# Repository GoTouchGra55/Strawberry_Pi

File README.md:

# 🍓 Strawberry Pi

A Raspberry Pi-4 form factor STM32 development board designed as a compact computing platform.

## Overview

Strawberry Pi is a custom 4-layer STM32-based development platform built around the **STM32H743** Cortex-M7 micro-controller.

The goal was to take the general concept of a small single-board computer and recreate it around a powerful micro-controller, integrating many useful interfaces and peripherals as possible into a compact Raspberry Pi 4 form factor.

The board is intended as a development and experimentation platform for hardware projects.

**SEE [SCHEMATICS](Strawberry_Pi-4.pdf)**

## Routing

## Features

### Core

- **STM32H743** Cortex-M7 MCU
- Up to **480 MHz** CPU clock
- MicroSD storage
- SWD debugging

### Connectivity

- **Ethernet**
- USB-C
- I2C
- SPI
- UART

### Multimedia

- Camera interface via **DCMI**
- Digital audio interface via **SAI**
- PCM1862 audio ADC
- 3.5 mm stereo audio input

### Power

The board provides dedicated:

- **5 V rail**
- **3.3 V rail**

## Rough BOM
| # | Item | Cost | Supplier |
|---|---|---:|---|
| 1 | PCB | $154.23 | JLCPCB |
| 2 | SMD Resistors | $8.35 | Daraz Nepal |
| 3 | SMD Capacitors | $7.98 | Daraz Nepal |
| | **Total** | **$170.56** | |

## Authors 👥

### Shaurya (Electronics)

Contact: [Email](shauryatamang.dev@gmail.com)

### Krish (CAD)

View: [Github](https://github.com/unknowngamer69/)

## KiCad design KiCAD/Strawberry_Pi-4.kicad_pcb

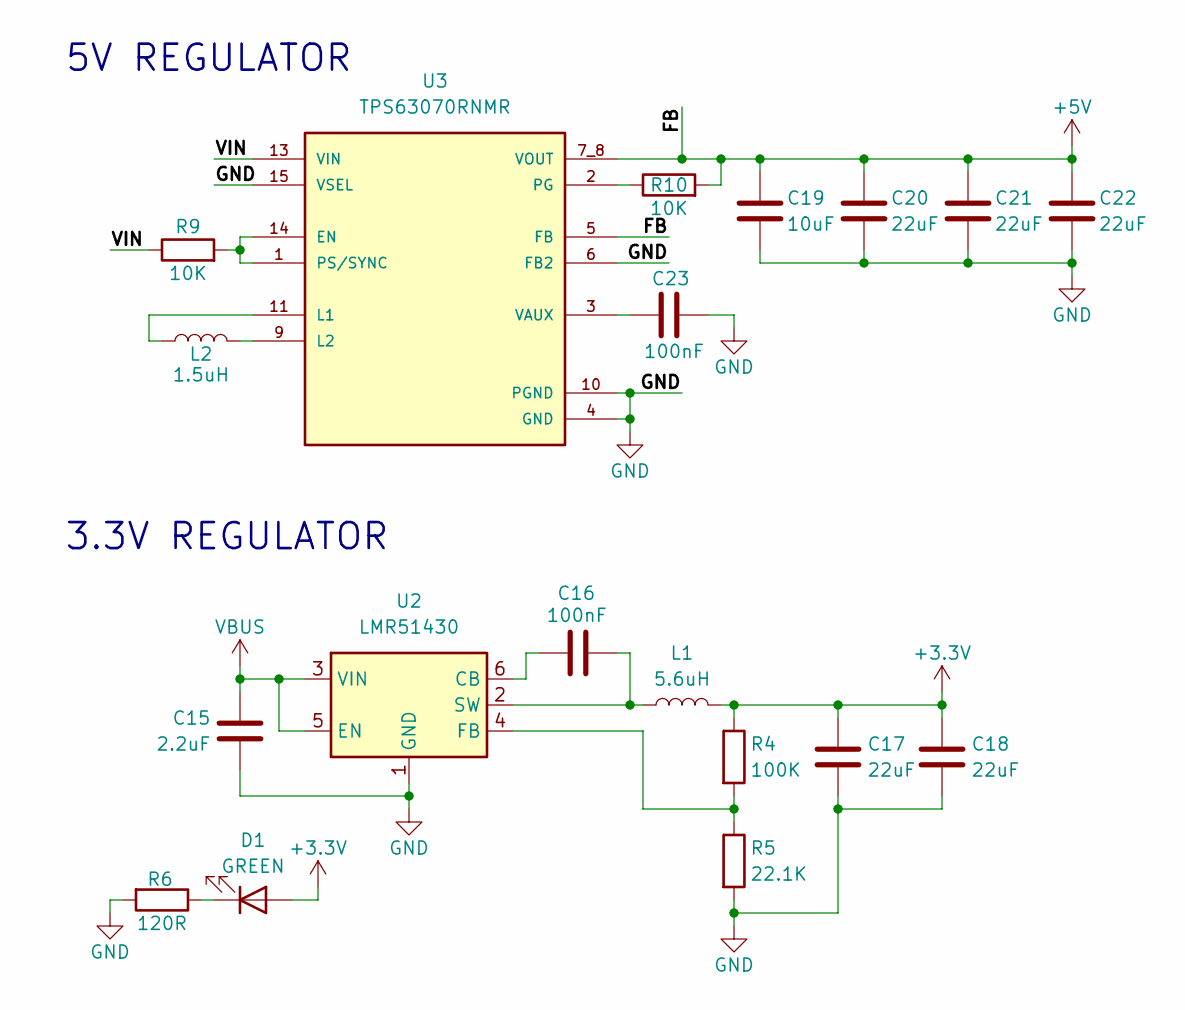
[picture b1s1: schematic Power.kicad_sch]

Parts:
C15: 2.2uF; C_0805_2012Metric
C16, C23: 100nF; C_0402_1005Metric
C17, C18, C20, C21, C22: 22uF; C_1210_3225Metric
C19: 10uF; C_0805_2012Metric
D1: GREEN; LED_0603_1608Metric
L1: 5.6uH; L_Wurth_WE-LQSH-2512
L2: 1.5uH; L_Wurth_WE-LQSH-4020
R4: 100K; R_0805_2012Metric
R5: 22.1K; R_0805_2012Metric
R6: 120R; R_0603_1608Metric
R9, R10: 10K; R_0603_1608Metric
U2: LMR51430; SOT-23-6
U3: TPS63070RNMR; VREG_TPS63070RNMR; PARTREV B

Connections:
+3.3V: C17.1, C18.1, D1.2 (A), L1.2, R4.1; also elsewhere on the board
+5V: C19.1, C20.1, C21.1, C22.1, R10.2, U3.5 (FB), U3.7_8 (VOUT); also elsewhere on the board
/Power/VIN: R9.1, U3.13 (VIN)
GND: C15.2, C17.2, C18.2, C19.2, C20.2, C21.2, C22.2, C23.2, R5.2, R6.2, U2.1 (GND), U3.4 (GND), U3.6 (FB2), U3.10 (PGND), U3.15 (VSEL); also elsewhere on the board
unnamed: D1.1 (K), R6.1
unnamed: C16.2, U2.6 (CB)
unnamed: R4.2, R5.1, U2.4 (FB)
unnamed: C16.1, L1.1, U2.2 (SW)
unnamed: R9.2, U3.1 (PS/SYNC), U3.14 (EN)
unnamed: L2.1, U3.11 (L1)
unnamed: L2.2, U3.9 (L2)
unnamed: R10.1, U3.2 (PG)
unnamed: C23.1, U3.3 (VAUX)
VBUS: C15.1, U2.3 (VIN), U2.5 (EN); also elsewhere on the board

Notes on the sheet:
5V REGULATOR
3.3V REGULATOR

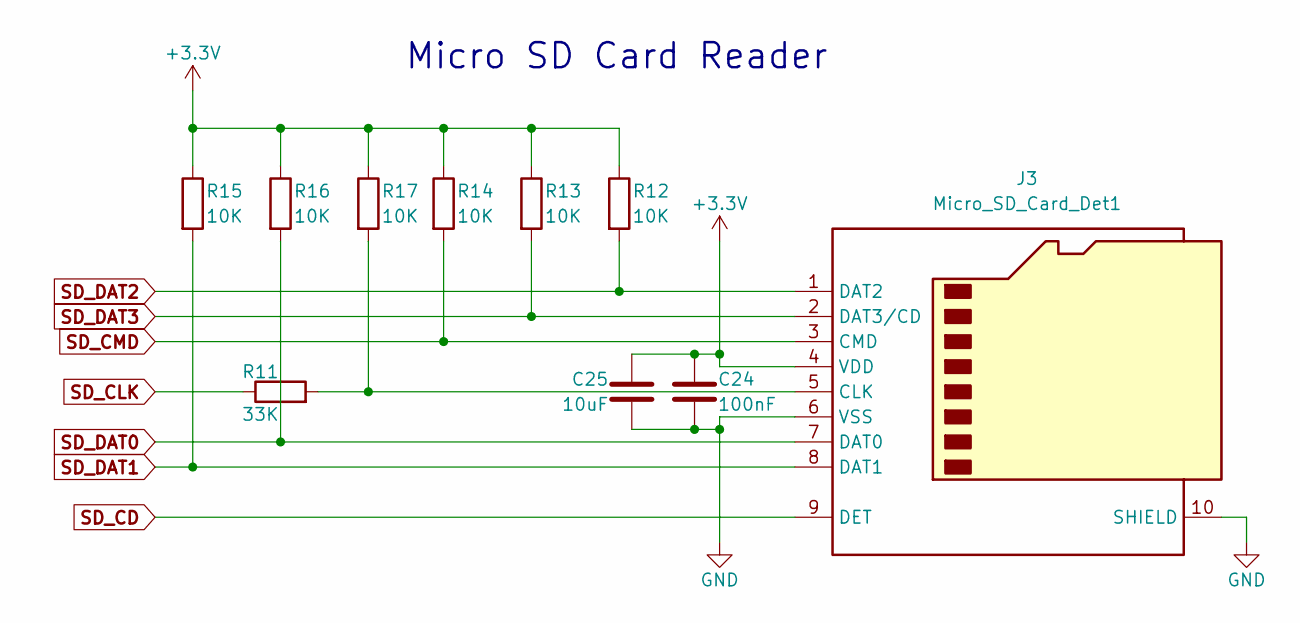
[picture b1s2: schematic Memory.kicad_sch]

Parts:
C24: 100nF; C_0402_1005Metric
C25: 10uF; C_0805_2012Metric
J3: Micro_SD_Card_Det1; microSD_HC_Wuerth
R11: 33K; R_0603_1608Metric
R12, R13, R14, R15, R16, R17: 10K; R_0603_1608Metric

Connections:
+3.3V: C24.1, C25.1, J3.4 (VDD), R12.1, R13.1, R14.1, R15.1, R16.1, R17.1; also elsewhere on the board
GND: C24.2, C25.2, J3.6 (VSS), J3.10 (SHIELD); also elsewhere on the board
unnamed: J3.5 (CLK), R11.2, R17.2
SD_CD: J3.9 (DET); also elsewhere on the board
SD_CLK: R11.1; also elsewhere on the board
SD_CMD: J3.3 (CMD), R14.2; also elsewhere on the board
SD_DAT0: J3.7 (DAT0), R16.2; also elsewhere on the board
SD_DAT1: J3.8 (DAT1), R15.2; also elsewhere on the board
SD_DAT2: J3.1 (DAT2), R12.2; also elsewhere on the board
SD_DAT3: J3.2 (DAT3/CD), R13.2; also elsewhere on the board

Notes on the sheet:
Micro SD Card Reader

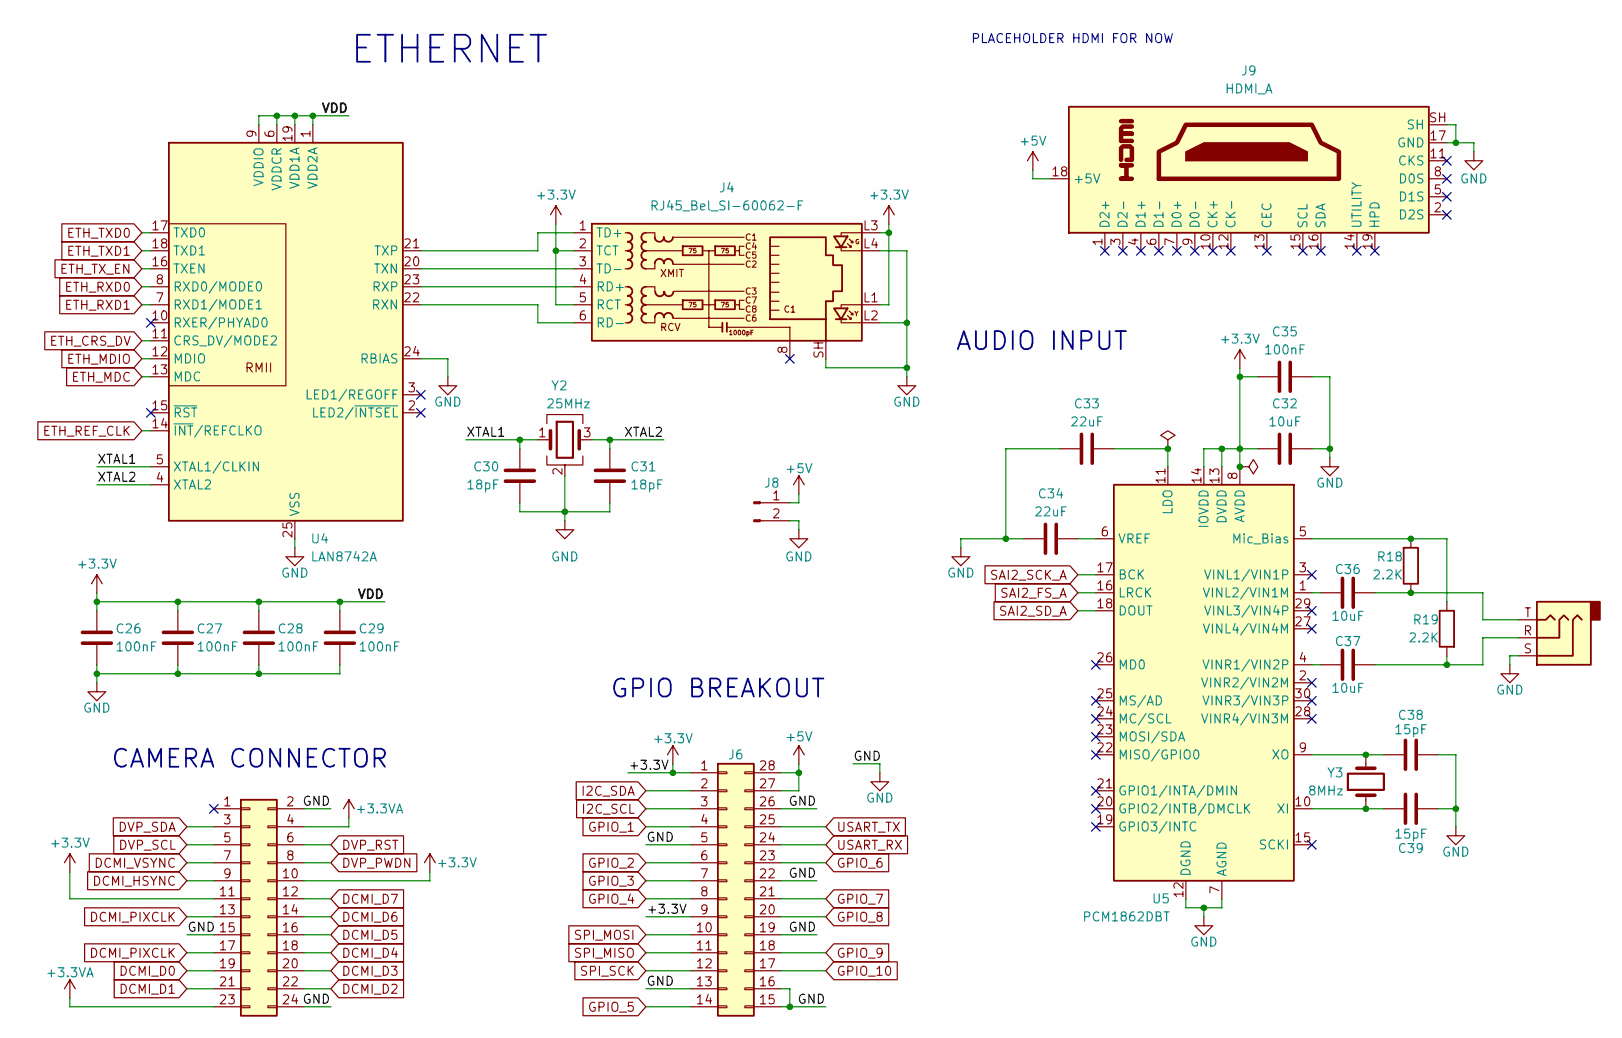
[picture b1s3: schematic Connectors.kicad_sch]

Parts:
C26, C27, C28, C29, C35: 100nF; C_0402_1005Metric
C30, C31: 18pF; C_0402_1005Metric
C32, C36, C37: 10uF; C_0805_2012Metric
C33, C34: 22uF; C_1210_3225Metric
C38, C39: 15pF; C_0402_1005Metric
J4: RJ45_Bel_SI-60062-F
J5: AudioJack3; Jack_3.5mm_CUI_SJ-3523-SMT_Horizontal
J6: Conn_02x14_Counter_Clockwise; PinHeader_2x14_P2.54mm_Vertical
J7: Conn_02x12_Odd_Even; PinHeader_2x12_P1.00mm_Vertical_SMD
J8: Conn_01x02_Pin; JST_EH_B2B-EH-A_1x02_P2.50mm_Vertical
J9: HDMI_A; HDMI_Micro-D_Molex_46765-1xxx
R18, R19: 2.2K; R_0603_1608Metric
U4: LAN8742A; VQFN-24-1EP_4x4mm_P0.5mm_EP2.5x2.5mm_ThermalVias
U5: PCM1862DBT; TSSOP-30_4.4x7.8mm_P0.5mm
Y2: 25MHz; Crystal_SMD_3225-4Pin_3.2x2.5mm
Y3: 8MHz; Crystal_SMD_3215-2Pin_3.2x1.5mm

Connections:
+3.3V: C26.1, C27.1, C28.1, C29.1, C32.2, C35.2, J4.2 (TCT), J4.5 (RCT), J4.L1, J4.L3, J6.1, J6.9, J7.10, J7.11, U4.1 (VDD2A), U4.6 (VDDCR), U4.9 (VDDIO), U4.19 (VDD1A), U5.8 (AVDD), U5.13 (DVDD), U5.14 (IOVDD); also elsewhere on the board
+3.3VA: J7.4, J7.23; also elsewhere on the board
+5V: J6.27, J6.28, J8.1, J9.18 (+5V); also elsewhere on the board
/Connectors/XTAL1: C30.1, U4.5 (XTAL1/CLKIN), Y2.1
/Connectors/XTAL2: C31.1, U4.4 (XTAL2), Y2.3
DCMI_D0: J7.19; also elsewhere on the board
DCMI_D1: J7.21; also elsewhere on the board
DCMI_D2: J7.22; also elsewhere on the board
DCMI_D3: J7.20; also elsewhere on the board
DCMI_D4: J7.18; also elsewhere on the board
DCMI_D5: J7.16; also elsewhere on the board
DCMI_D6: J7.14; also elsewhere on the board
DCMI_D7: J7.12; also elsewhere on the board
DCMI_HSYNC: J7.9; also elsewhere on the board
DCMI_PIXCLK: J7.13, J7.17; also elsewhere on the board
DCMI_VSYNC: J7.7; also elsewhere on the board
DVP_PWDN: J7.8
DVP_RST: J7.6
DVP_SCL: J7.5
DVP_SDA: J7.3
ETH_CRS_DV: U4.11 (CRS_DV/MODE2); also elsewhere on the board
ETH_MDC: U4.13 (MDC); also elsewhere on the board
ETH_MDIO: U4.12 (MDIO); also elsewhere on the board
ETH_REF_CLK: U4.14 (~INT/REFCLKO); also elsewhere on the board
ETH_RXD0: U4.8 (RXD0/MODE0); also elsewhere on the board
ETH_RXD1: U4.7 (RXD1/MODE1); also elsewhere on the board
ETH_TXD0: U4.17 (TXD0); also elsewhere on the board
ETH_TXD1: U4.18 (TXD1); also elsewhere on the board
ETH_TX_EN: U4.16 (TXEN); also elsewhere on the board
GND: C26.2, C27.2, C28.2, C29.2, C30.2, C31.2, C32.1, C33.2, C34.2, C35.1, C38.1, C39.1, J4.L2, J4.L4, J4.SH, J5.S, J6.5, J6.13, J6.15, J6.16, J6.19, J6.22, J6.26, J7.2, J7.15, J7.24, J8.2, J9.17 (GND), J9.SH, U4.24 (RBIAS), U4.25 (VSS), U5.7 (AGND), U5.12 (DGND), Y2.2 (G), Y2.4 (G); also elsewhere on the board
GPIO_1: J6.4; also elsewhere on the board
GPIO_2: J6.6; also elsewhere on the board
GPIO_3: J6.7; also elsewhere on the board
GPIO_4: J6.8; also elsewhere on the board
GPIO_5: J6.14; also elsewhere on the board
GPIO_6: J6.23; also elsewhere on the board
GPIO_7: J6.21; also elsewhere on the board
GPIO_8: J6.20; also elsewhere on the board
GPIO_9: J6.18; also elsewhere on the board
GPIO_10: J6.17; also elsewhere on the board
I2C_SCL: J6.3; also elsewhere on the board
I2C_SDA: J6.2; also elsewhere on the board
unnamed: C36.1, J5.T, R18.1
unnamed: C37.1, J5.R, R19.2
unnamed: J4.4 (RD+), U4.23 (RXP)
unnamed: J4.6 (RD-), U4.22 (RXN)
unnamed: J4.1 (TD+), U4.21 (TXP)
unnamed: J4.3 (TD-), U4.20 (TXN)
unnamed: C33.1, U5.11 (LDO)
unnamed: R18.2, R19.1, U5.5 (Mic_Bias)
unnamed: C36.2, U5.1 (VINL2/VIN1M)
unnamed: C37.2, U5.4 (VINR1/VIN2P)
unnamed: C34.1, U5.6 (VREF)
unnamed: C39.2, U5.10 (XI), Y3.1
unnamed: C38.2, U5.9 (XO), Y3.2
SAI2_FS_A: U5.16 (LRCK); also elsewhere on the board
SAI2_SCK_A: U5.17 (BCK); also elsewhere on the board
SAI2_SD_A: U5.18 (DOUT); also elsewhere on the board
SPI_MISO: J6.11; also elsewhere on the board
SPI_MOSI: J6.10; also elsewhere on the board
SPI_SCK: J6.12; also elsewhere on the board
USART_RX: J6.24; also elsewhere on the board
USART_TX: J6.25; also elsewhere on the board

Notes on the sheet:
GPIO BREAKOUT
PLACEHOLDER HDMI FOR NOW
ETHERNET
CAMERA CONNECTOR
AUDIO INPUT

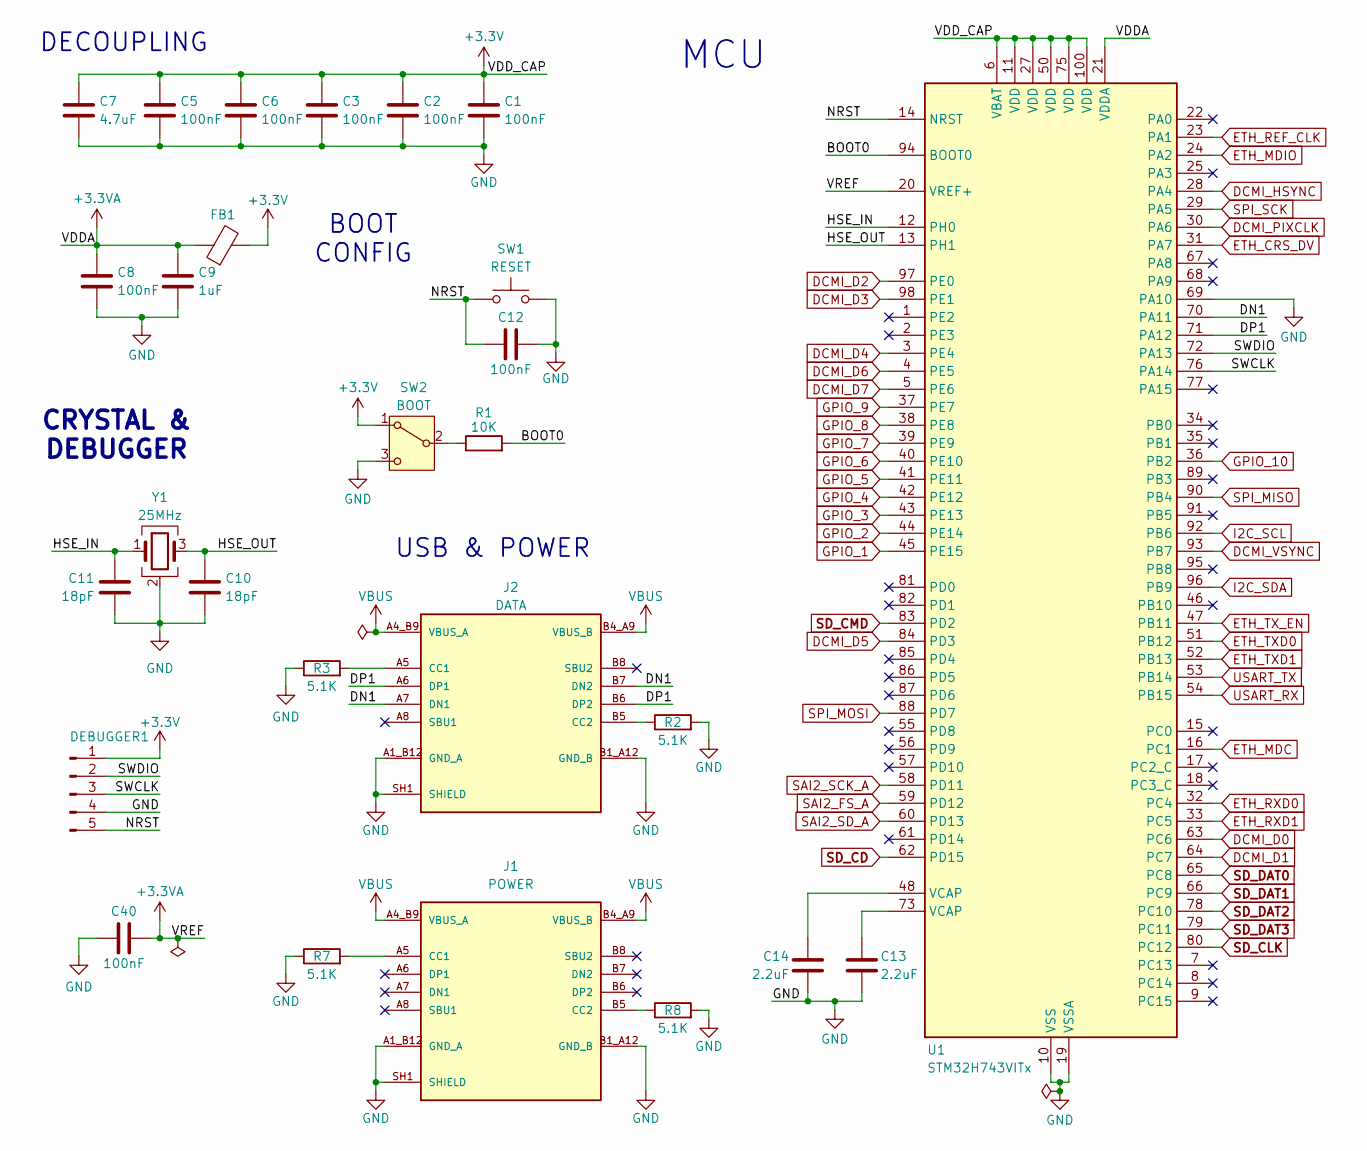
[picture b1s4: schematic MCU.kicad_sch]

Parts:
C1, C2, C3, C5, C6, C8, C12, C40: 100nF; C_0402_1005Metric
C7: 4.7uF; C_0805_2012Metric
C9: 1uF; C_0805_2012Metric
C10, C11: 18pF; C_0402_1005Metric
C13, C14: 2.2uF; C_0805_2012Metric
DEBUGGER1: Conn_01x05_Pin; JST_EH_S5B-EH_1x05_P2.50mm_Horizontal
FB1: FerriteBead; D_0603_1608Metric
J1: POWER; SHOUHAN_TYPE-C_16PIN_2MD__073_; PARTREV A
J2: DATA; SHOUHAN_TYPE-C_16PIN_2MD__073_; PARTREV A
R1: 10K; R_0603_1608Metric
R2, R3, R7, R8: 5.1K; R_0603_1608Metric
SW1: RESET; SW_Push_SPST_NO_Alps_SKRK
SW2: BOOT; SW_SPDT_PCM12
U1: STM32H743VITx; LQFP-100_14x14mm_P0.5mm
Y1: 25MHz; Crystal_SMD_3225-4Pin_3.2x2.5mm

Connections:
+3.3V: C1.1, C2.1, C3.1, C5.1, C6.1, C7.1, DEBUGGER1.1, FB1.2, SW2.1 (A), U1.6 (VBAT), U1.11 (VDD), U1.27 (VDD), U1.50 (VDD), U1.75 (VDD), U1.100 (VDD); also elsewhere on the board
+3.3VA: C8.1, C9.1, C40.1, FB1.1, U1.20 (VREF+), U1.21 (VDDA); also elsewhere on the board
/MCU/BOOT0: R1.2, U1.94 (BOOT0)
/MCU/DN1: J2.A7 (DN1), J2.B7 (DN2), U1.70 (PA11)
/MCU/DP1: J2.A6 (DP1), J2.B6 (DP2), U1.71 (PA12)
/MCU/HSE_IN: C11.1, U1.12 (PH0), Y1.1
/MCU/HSE_OUT: C10.1, U1.13 (PH1), Y1.3
/MCU/NRST: C12.2, DEBUGGER1.5, SW1.2, U1.14 (NRST)
/MCU/SWCLK: DEBUGGER1.3, U1.76 (PA14)
/MCU/SWDIO: DEBUGGER1.2, U1.72 (PA13)
DCMI_D0: U1.63 (PC6); also elsewhere on the board
DCMI_D1: U1.64 (PC7); also elsewhere on the board
DCMI_D2: U1.97 (PE0); also elsewhere on the board
DCMI_D3: U1.98 (PE1); also elsewhere on the board
DCMI_D4: U1.3 (PE4); also elsewhere on the board
DCMI_D5: U1.84 (PD3); also elsewhere on the board
DCMI_D6: U1.4 (PE5); also elsewhere on the board
DCMI_D7: U1.5 (PE6); also elsewhere on the board
DCMI_HSYNC: U1.28 (PA4); also elsewhere on the board
DCMI_PIXCLK: U1.30 (PA6); also elsewhere on the board
DCMI_VSYNC: U1.93 (PB7); also elsewhere on the board
ETH_CRS_DV: U1.31 (PA7); also elsewhere on the board
ETH_MDC: U1.16 (PC1); also elsewhere on the board
ETH_MDIO: U1.24 (PA2); also elsewhere on the board
ETH_REF_CLK: U1.23 (PA1); also elsewhere on the board
ETH_RXD0: U1.32 (PC4); also elsewhere on the board
ETH_RXD1: U1.33 (PC5); also elsewhere on the board
ETH_TXD0: U1.51 (PB12); also elsewhere on the board
ETH_TXD1: U1.52 (PB13); also elsewhere on the board
ETH_TX_EN: U1.47 (PB11); also elsewhere on the board
GND: C1.2, C2.2, C3.2, C5.2, C6.2, C7.2, C8.2, C9.2, C10.2, C11.2, C12.1, C13.2, C14.2, C40.2, DEBUGGER1.4, J1.A1_B12 (GND_A), J1.B1_A12 (GND_B), J1.SH1 (SHIELD), J1.SH2 (SHIELD), J1.SH3 (SHIELD), J1.SH4 (SHIELD), J2.A1_B12 (GND_A), J2.B1_A12 (GND_B), J2.SH1 (SHIELD), J2.SH2 (SHIELD), J2.SH3 (SHIELD), J2.SH4 (SHIELD), R2.2, R3.1, R7.1, R8.2, SW1.1, SW2.3 (C), U1.10 (VSS), U1.19 (VSSA), U1.26 (VSS), U1.49 (VSS), U1.69 (PA10), U1.74 (VSS), U1.99 (VSS), Y1.2 (G), Y1.4 (G); also elsewhere on the board
GPIO_1: U1.45 (PE15); also elsewhere on the board
GPIO_2: U1.44 (PE14); also elsewhere on the board
GPIO_3: U1.43 (PE13); also elsewhere on the board
GPIO_4: U1.42 (PE12); also elsewhere on the board
GPIO_5: U1.41 (PE11); also elsewhere on the board
GPIO_6: U1.40 (PE10); also elsewhere on the board
GPIO_7: U1.39 (PE9); also elsewhere on the board
GPIO_8: U1.38 (PE8); also elsewhere on the board
GPIO_9: U1.37 (PE7); also elsewhere on the board
GPIO_10: U1.36 (PB2); also elsewhere on the board
I2C_SCL: U1.92 (PB6); also elsewhere on the board
I2C_SDA: U1.96 (PB9); also elsewhere on the board
unnamed: C13.1, U1.73 (VCAP)
unnamed: C14.1, U1.48 (VCAP)
unnamed: J1.A5 (CC1), R7.2
unnamed: J1.B5 (CC2), R8.1
unnamed: J2.A5 (CC1), R3.2
unnamed: J2.B5 (CC2), R2.1
unnamed: R1.1, SW2.2 (B)
SAI2_FS_A: U1.59 (PD12); also elsewhere on the board
SAI2_SCK_A: U1.58 (PD11); also elsewhere on the board
SAI2_SD_A: U1.60 (PD13); also elsewhere on the board
SD_CD: U1.62 (PD15); also elsewhere on the board
SD_CLK: U1.80 (PC12); also elsewhere on the board
SD_CMD: U1.83 (PD2); also elsewhere on the board
SD_DAT0: U1.65 (PC8); also elsewhere on the board
SD_DAT1: U1.66 (PC9); also elsewhere on the board
SD_DAT2: U1.78 (PC10); also elsewhere on the board
SD_DAT3: U1.79 (PC11); also elsewhere on the board
SPI_MISO: U1.90 (PB4); also elsewhere on the board
SPI_MOSI: U1.88 (PD7); also elsewhere on the board
SPI_SCK: U1.29 (PA5); also elsewhere on the board
USART_RX: U1.54 (PB15); also elsewhere on the board
USART_TX: U1.53 (PB14); also elsewhere on the board
VBUS: J1.A4_B9 (VBUS_A), J1.B4_A9 (VBUS_B), J2.A4_B9 (VBUS_A), J2.B4_A9 (VBUS_B); also elsewhere on the board

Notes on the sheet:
DECOUPLING
CRYSTAL & DEBUGGER
USB & POWER
BOOT CONFIG
MCU

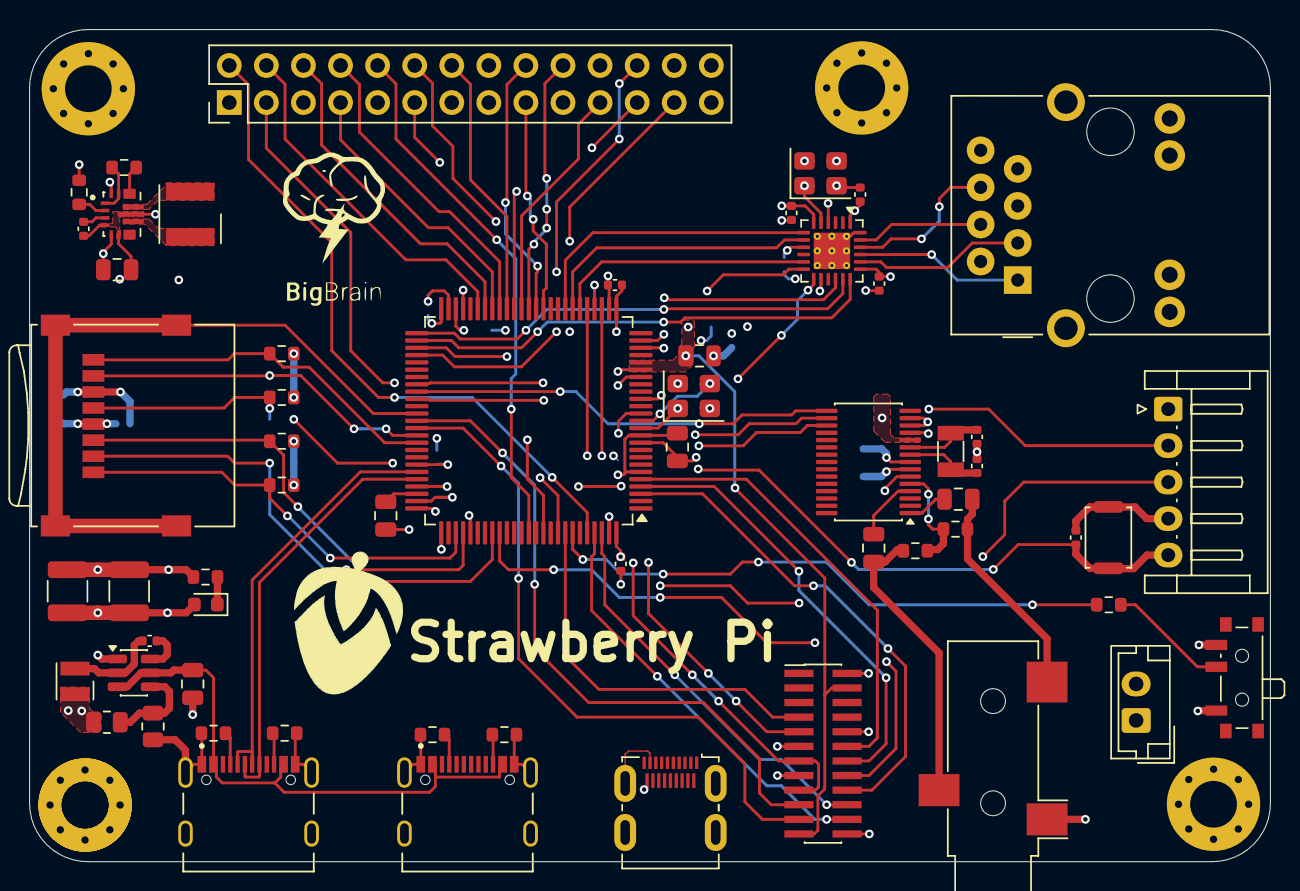
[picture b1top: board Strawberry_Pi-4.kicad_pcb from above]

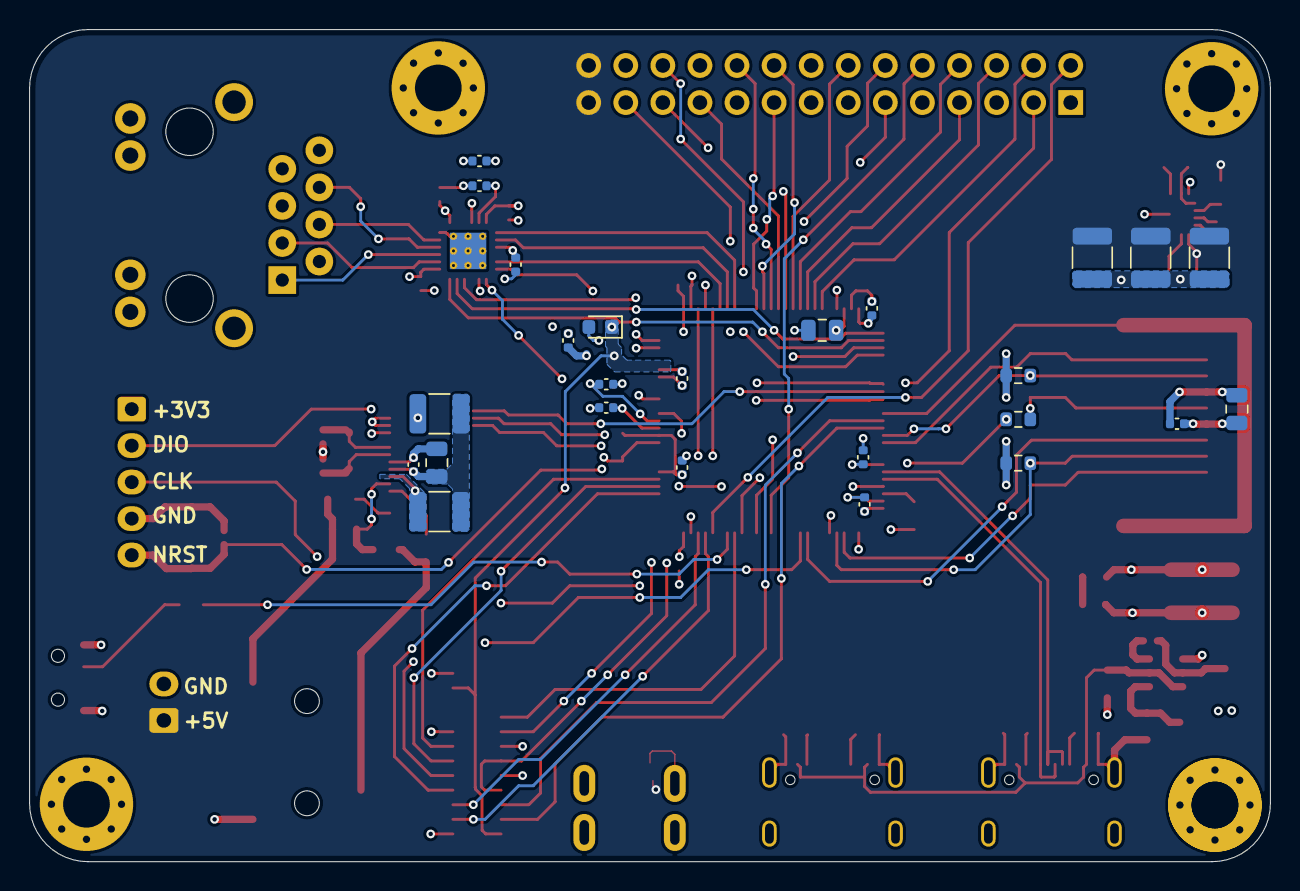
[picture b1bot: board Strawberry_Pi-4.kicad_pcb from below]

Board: 4 copper layers, 85.0 x 57.0 mm, 83 parts (25 on the bottom side), 93 nets.

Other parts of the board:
C4: 100nF; C_0402_1005Metric

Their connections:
+3.3V: C4.1; also elsewhere on the board
GND: C4.2; also elsewhere on the board

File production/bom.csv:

Designator,Footprint,Quantity,Value,LCSC Part #
,,1,,
"C1, C12, C16, C2, C23, C24, C26, C27, C28, C29, C3, C35, C4, C40, C5, C6, C8",0402,17,100nF,
"C10, C11, C30, C31",0402,4,18pF,
"C13, C14, C15",0805,3,2.2uF,
"C17, C18, C20, C21, C22, C33, C34",1210,7,22uF,
"C19, C25, C32, C36, C37",0805,5,10uF,
"C38, C39",0402,2,15pF,
C7,0805,1,4.7uF,
C9,0805,1,1uF,
D1,0603,1,GREEN,
DEBUGGER1,JST_EH_S5B-EH_1x05_P2.50mm_Horizontal,1,Conn_01x05_Pin,
FB1,0603,1,FerriteBead,
J1,SHOUHAN_TYPE-C_16PIN_2MD__073_,1,POWER,
J2,SHOUHAN_TYPE-C_16PIN_2MD__073_,1,DATA,
J3,microSD_HC_Wuerth,1,Micro_SD_Card_Det1,
J4,RJ45_Bel_SI-60062-F,1,RJ45_Bel_SI-60062-F,
J5,Jack_3.5mm_CUI_SJ-3523-SMT_Horizontal,1,AudioJack3,
J6,PinHeader_2x14_P2.54mm_Vertical,1,Conn_02x14_Counter_Clockwise,
J7,PinHeader_2x12_P1.00mm_Vertical_SMD,1,Conn_02x12_Odd_Even,
J8,JST_EH_B2B-EH-A_1x02_P2.50mm_Vertical,1,Conn_01x02_Pin,
J9,HDMI_Micro-D_Molex_46765-1xxx,1,HDMI_A,
L1,L_Wurth_WE-LQSH-2512,1,5.6uH,
L2,L_Wurth_WE-LQSH-4020,1,1.5uH,
"R1, R10, R12, R13, R14, R15, R16, R17, R9",0603,9,10K,
R11,0603,1,33K,
"R18, R19",0603,2,2.2K,
"R2, R3, R7, R8",0603,4,5.1K,
R4,0805,1,100K,
R5,0805,1,22.1K,
R6,0603,1,120R,
SW1,SW_Push_SPST_NO_Alps_SKRK,1,RESET,
SW2,SW_SPDT_PCM12,1,BOOT,
U1,LQFP-100_14x14mm_P0.5mm,1,STM32H743VITx,
U2,SOT-23-6,1,LMR51430,
U3,VREG_TPS63070RNMR,1,TPS63070RNMR,
U4,VQFN-24-1EP_4x4mm_P0.5mm_EP2.5x2.5mm_ThermalVias,1,LAN8742A,
U5,TSSOP-30_4.4x7.8mm_P0.5mm,1,PCM1862DBT,
"Y1, Y2",Crystal_SMD_3225-4Pin_3.2x2.5mm,2,25MHz,
Y3,Crystal_SMD_3215-2Pin_3.2x1.5mm,1,8MHz,
